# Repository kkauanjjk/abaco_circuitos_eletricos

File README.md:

# abaco_circuitos_eletricos
Repositório dedicado aos recursos utilizados e produzidos durante o projeto da disciplina de Circuitos Elétricos I

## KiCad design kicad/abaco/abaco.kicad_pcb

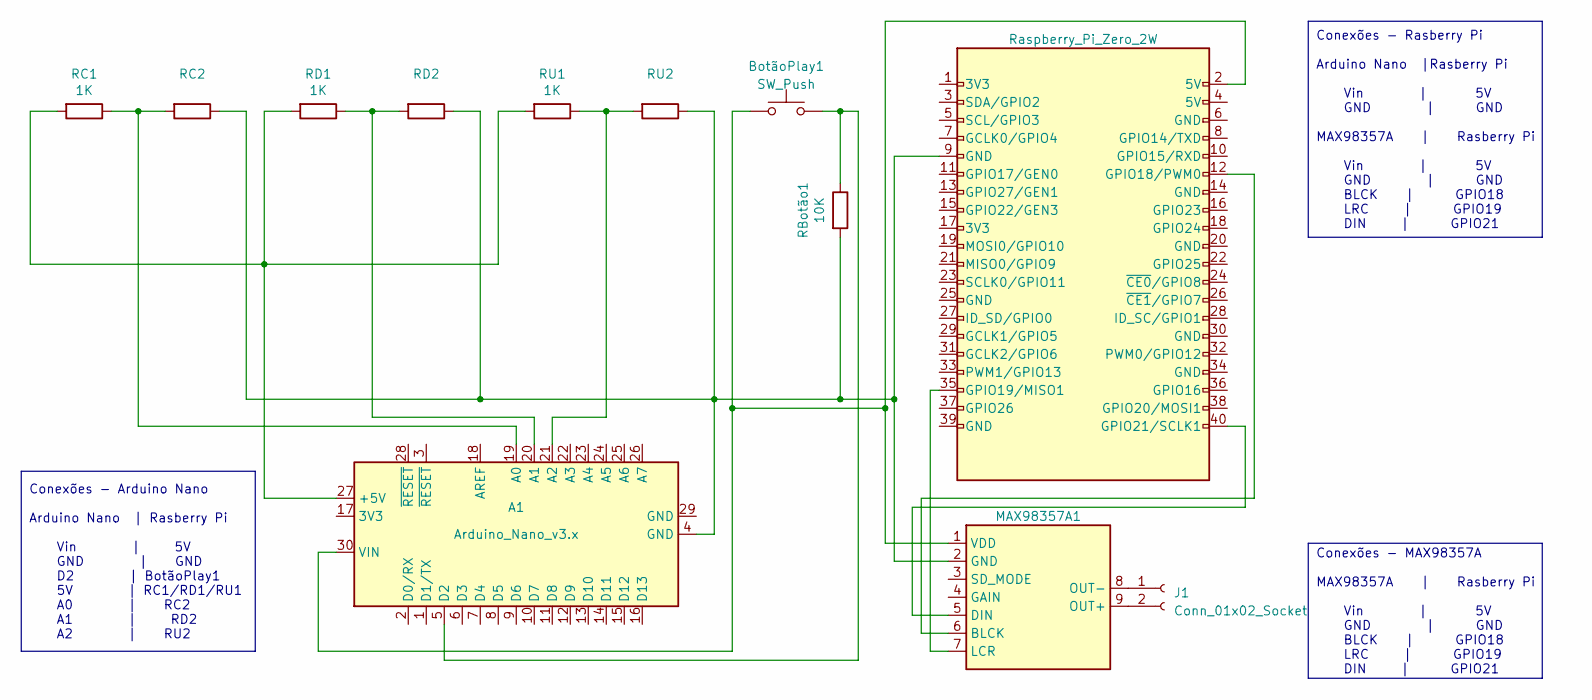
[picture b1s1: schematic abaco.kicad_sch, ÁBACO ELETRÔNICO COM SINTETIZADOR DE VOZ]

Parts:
A1: Arduino_Nano_v3.x; Arduino_Nano
BotãoPlay1: SW_Push; SW_PUSH_6mm_H4.3mm
J1: Conn_01x02_Socket
MAX98357A1: PinHeader_1x07_P2.54mm_Vertical
RBotão1: 10K; R_Axial_DIN0411_L9.9mm_D3.6mm_P12.70mm_Horizontal
RC1: 1K; R_Axial_DIN0411_L9.9mm_D3.6mm_P12.70mm_Horizontal
RC2: 1K; R_Axial_DIN0411_L9.9mm_D3.6mm_P25.40mm_Horizontal
RD1: 1K; R_Axial_DIN0411_L9.9mm_D3.6mm_P12.70mm_Horizontal
RD2: 1K; R_Axial_DIN0411_L9.9mm_D3.6mm_P25.40mm_Horizontal
RU1: 1K; R_Axial_DIN0411_L9.9mm_D3.6mm_P12.70mm_Horizontal
RU2: 1K; R_Axial_DIN0411_L9.9mm_D3.6mm_P25.40mm_Horizontal
https://datasheets.raspberrypi.com/rpizero2/raspberry-pi-zero-2-w-reduced-schematics.pdf1: Raspberry_Pi_Zero_2W; Raspberry_Pi_Zero_Socketed_THT_FaceDown_MountingHoles

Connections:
unnamed: A1.27 (+5V), RC1.2, RD1.2, RU1.2
unnamed: A1.19 (A0), RC1.1, RC2.2
unnamed: A1.20 (A1), RD1.1, RD2.2
unnamed: A1.21 (A2), RU1.1, RU2.2
unnamed: A1.5 (D2), BotãoPlay1.2, RBotão1.1
unnamed: A1.30 (VIN), BotãoPlay1.1, MAX98357A1.1 (VDD), https://datasheets.raspberrypi.com/rpiz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.2 (5V)
unnamed: J1.1, MAX98357A1.8 (OUT-)
unnamed: J1.2, MAX98357A1.9 (OUT+)
unnamed: MAX98357A1.6 (BLCK), https://datasheets.raspberrypi.com/rpiz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.12 (GPIO18/PWM0)
unnamed: MAX98357A1.5 (DIN), https://datasheets.raspberrypi.com/rpiz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.40 (GPIO21/SCLK1)
unnamed: A1.4 (GND), MAX98357A1.2 (GND), RBotão1.2, RC2.1, RD2.1, RU2.1, https://datasheets.raspberrypi.com/rpiz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.9 (GND)
unnamed: MAX98357A1.7 (LCR), https://datasheets.raspberrypi.com/rpiz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.35 (GPIO19/MISO1)

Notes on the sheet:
Conexões - MAX98357A MAX98357A | Rasberry Pi Vin | 5V GND | GND BLCK | GPIO18 LRC | GPIO19 DIN | GPIO21
Conexões - Arduino Nano Arduino Nano | Rasberry Pi Vin | 5V GND | GND D2 | BotãoPlay1 5V | RC1/RD1/RU1 A0 | RC2 A1 | RD2 A2 | RU2
Conexões - Rasberry Pi Arduino Nano |Rasberry Pi Vin | 5V GND | GND MAX98357A | Rasberry Pi Vin | 5V GND | GND BLCK | GPIO18 LRC | GPIO19 DIN | GPIO21

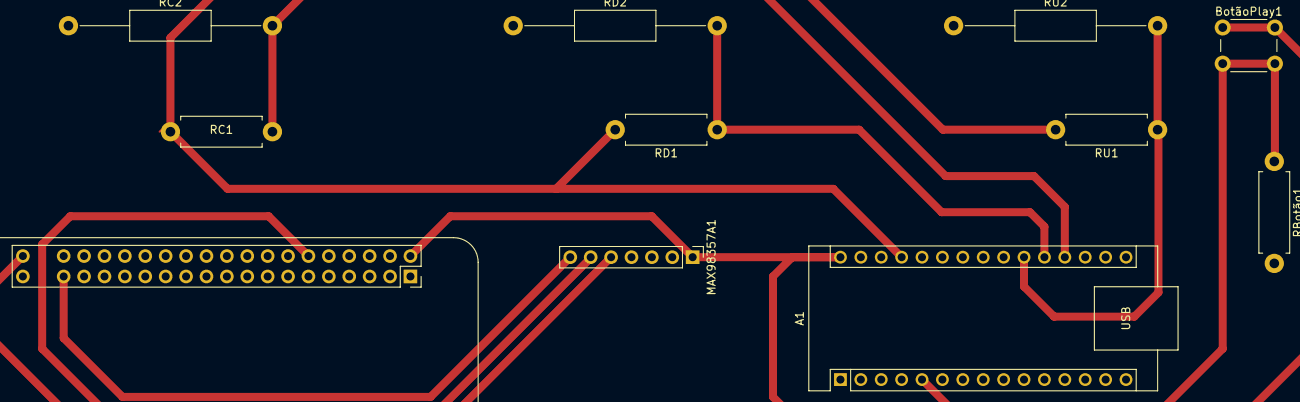
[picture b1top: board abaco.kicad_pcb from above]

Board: 2 copper layers, 11 parts (0 on the bottom side), 10 nets.

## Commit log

2023-10-28 Python | Code | v1.0
